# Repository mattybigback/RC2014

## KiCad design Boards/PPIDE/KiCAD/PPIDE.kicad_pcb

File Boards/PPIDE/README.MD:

# PPIDE - 8 bit IDE interface for RC2014

This module is an 8-bit IDE interface based around the 82C55 chip. The design was influenced by the IDE portion of the DiskIO v3 board for the N8VEM/Retrobrew platform. Address decoding is achieved by means of a 74HCT688 comparator.

## Getting up and running

The board will work with [Dr Baker's RomWBW fork](https://github.com/sbelectronics/RomWBW) fork by configuring the PPIDE driver in the platform configuration file. This is achieved by adding the following code to the platform configuration file, located at ```/Source/HBIOS/Config/plt_smb.asm```. If there is already an entry for PPIDE then replace it.

```
PPIDEENABLE     .EQU    FALSE    
PPIDEMODE       .EQU    PPIDEMODE_DIO3  
PPIDETRACE      .EQU    1              
PPIDE8BIT       .EQU    FALSE    
```

You must also add this line to your build config file to enable the PPIDE driver, as it is disabled by default. Build config files are located in the same directory as the platform config files.
```
PPIDEENABLE     .SET    TRUE
```

RomWBW expects the PPIDE hardware to be at haddress 0x20, so by defalt the DIP switches should be set so that A5 is on and the rest are off. You can change the base address in ```/Source/HBIOS/ppide.asm``` by modifying this block of code:

```
#IF (PPIDEMODE == PPIDEMODE_DIO3)
PPIDE_IO_BASE	.EQU	$20
#ENDIF
```

## Board features

* 40 pin IDE for standard desktop IDE drives
* Onboard HDD activity LED
* Header pin for external HDD activity LED
* 5v supply to IDE pin 20 (enabled by bridging JP1)
* Port address selectable by DIP switch

## Bill of materials

| Designator | Component |
|---|---|
| U1 | 74HCT688 |
| U2 | 82C55AZ |
| U3 | 74HCT14 (74HCT04 also suitable) |
| C1 - C3 | 100 nf ceramic capacitor |
| R1 - R2 | 470 Ω |
| R3 - R5 | 10 k |
| RN1 | 10k x 6 resistor network |
| SW1 | 6 way DIP switch |
| P1 | 1 x 39 0.1" right angle pin header |
| P2 | 2 x 20 0.1" right angle pin header |
| P3 | 1 x 2 0.1" straight pin header |
| JP1 | 1 x 2 0.1" straight pin header |
| D1 | 5mm LED |

## Board preview

![alt text][logo]

[logo]: https://github.com/mattybigback/RC2014/blob/master/Boards/PPIDE/PPIDE_small.png "PPIDE Board Render"

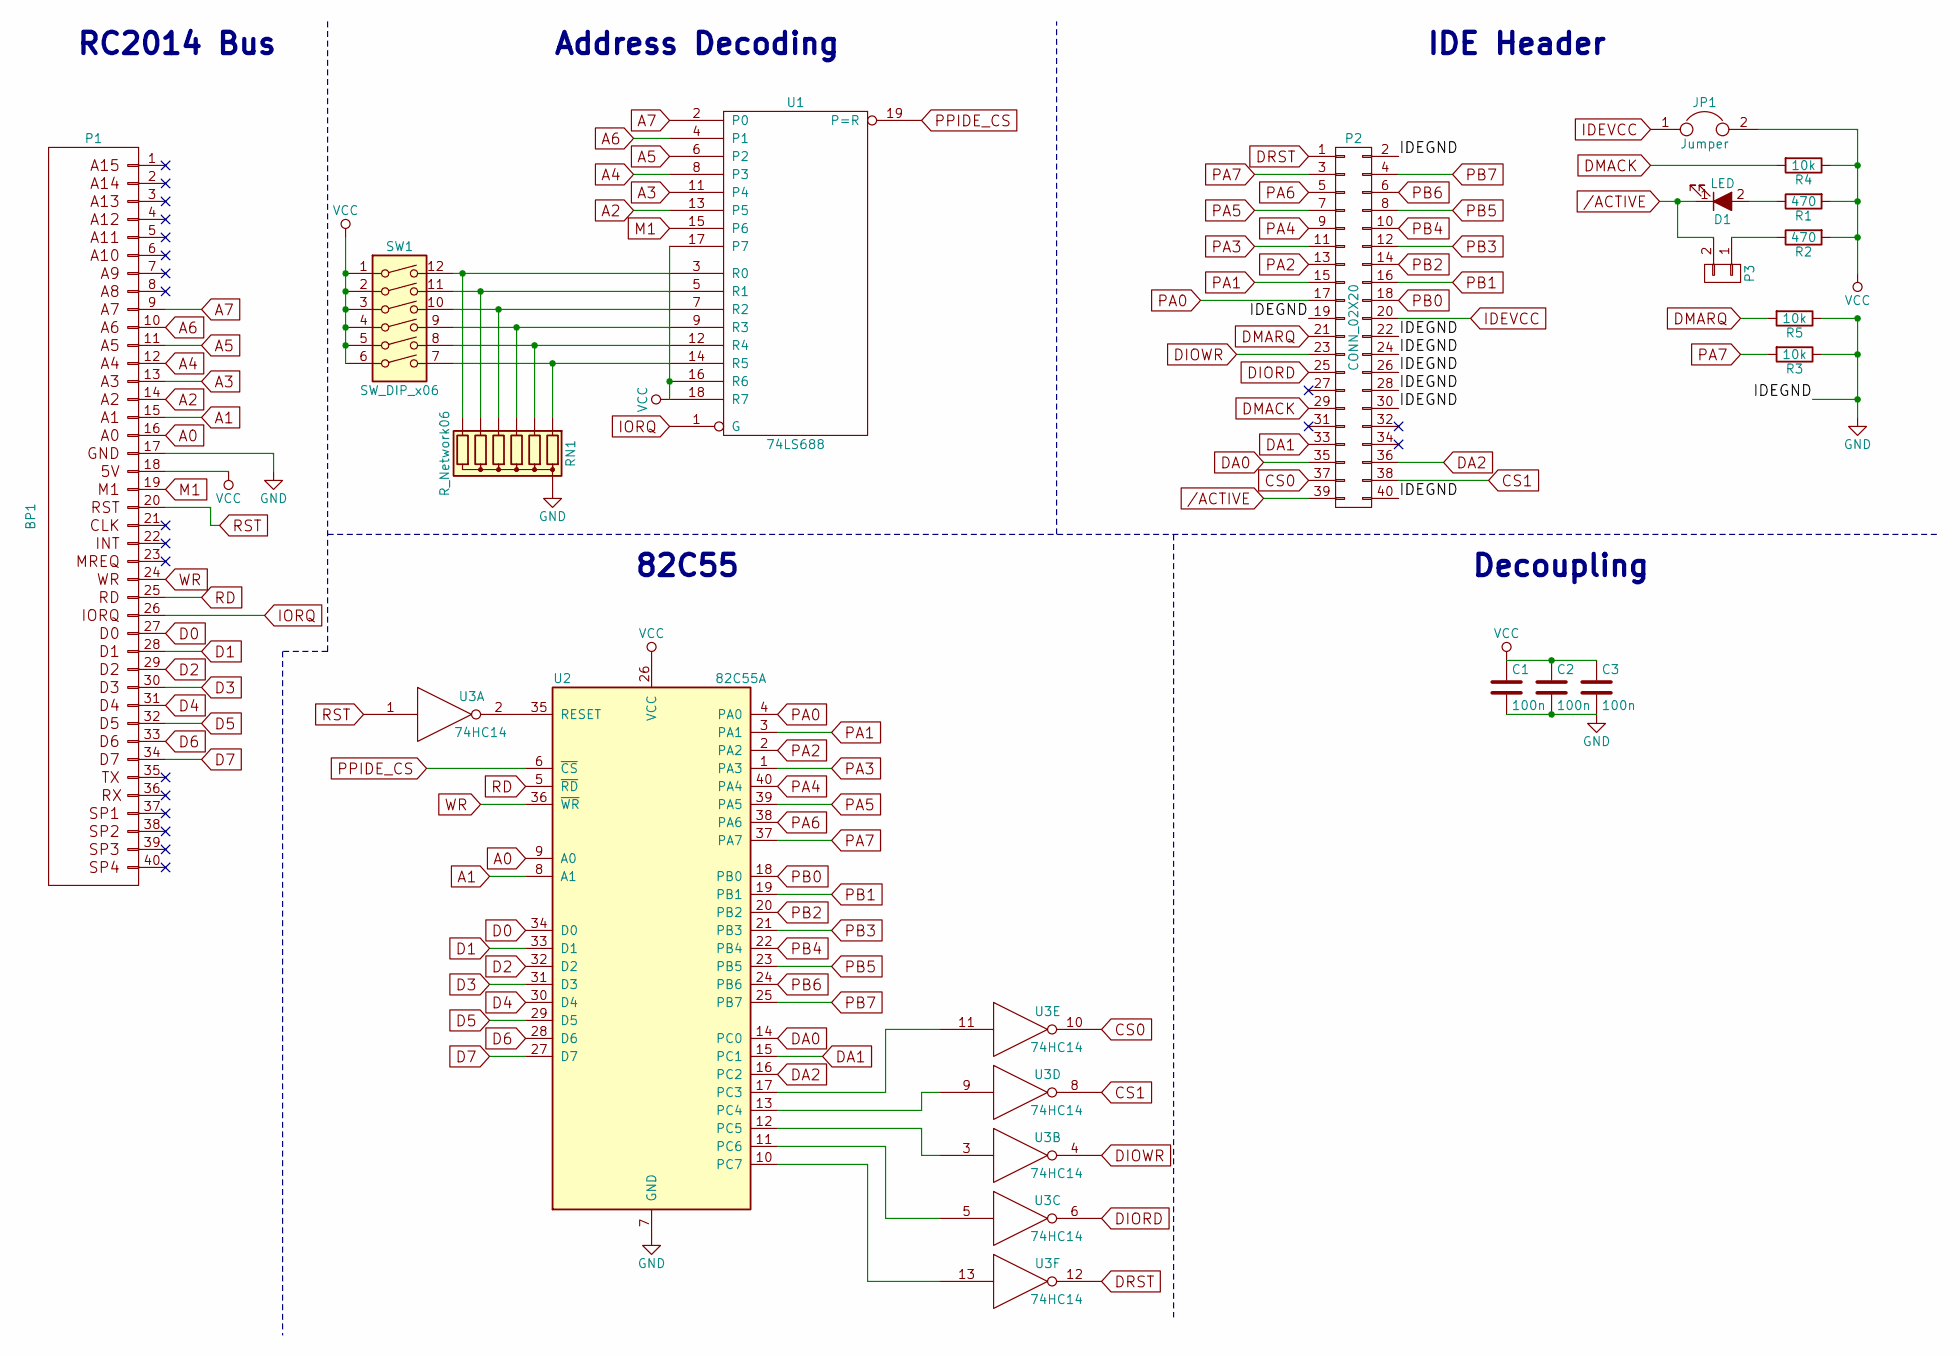
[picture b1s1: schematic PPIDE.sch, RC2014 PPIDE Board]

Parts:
C1, C2, C3: 100n; C_Disc_D10.0mm_W2.5mm_P5.00mm
D1: LED; LED_D5.0mm_FlatTop
JP1: Jumper; Pin_Header_Straight_1x02_Pitch2.54mm
P1: BP1; Pin_Header_Straight_1x39_Pitch2.54mm
P2: CONN_02X20; IDC_Header_Straight_40pins
P3: CONN_01X02; Pin_Header_Straight_1x02_Pitch2.54mm
R1, R2: 470; R_Axial_DIN0207_L6.3mm_D2.5mm_P10.16mm_Horizontal
R3, R4, R5: 10k; R_Axial_DIN0207_L6.3mm_D2.5mm_P10.16mm_Horizontal
RN1: R_Network06; R_Array_SIP7
SW1: SW_DIP_x06; SW_DIP_x6_W7.62mm_Slide
U1: 74LS688; DIP-20_W7.62mm_Socket_LongPads
U2: 82C55A; DIP-40_W15.24mm
U3: 74HC14; DIP-14_W7.62mm_Socket_LongPads

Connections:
/ACTIVE: D1.1 (K), P2.39, P3.2
A0: P1.16, U2.9 (A0)
A1: P1.15, U2.8 (A1)
A2: P1.14, U1.13 (P5)
A3: P1.13, U1.11 (P4)
A4: P1.12, U1.8 (P3)
A5: P1.11, U1.6 (P2)
A6: P1.10, U1.4 (P1)
A7: P1.9, U1.2 (P0)
CS0: P2.37, U3.10
CS1: P2.38, U3.8
D0: P1.27, U2.34 (D0)
D1: P1.28, U2.33 (D1)
D2: P1.29, U2.32 (D2)
D3: P1.30, U2.31 (D3)
D4: P1.31, U2.30 (D4)
D5: P1.32, U2.29 (D5)
D6: P1.33, U2.28 (D6)
D7: P1.34, U2.27 (D7)
DA0: P2.35, U2.14 (PC0)
DA1: P2.33, U2.15 (PC1)
DA2: P2.36, U2.16 (PC2)
DIORD: P2.25, U3.6
DIOWR: P2.23, U3.4
DMACK: P2.29, R4.2
DMARQ: P2.21, R5.2
DRST: P2.1, U3.12
GND: C1.2, C2.2, C3.2, P1.17, P2.2, P2.19, P2.22, P2.24, P2.26, P2.28, P2.30, P2.40, R3.1, R5.1, RN1.1 (common), U1.10 (GND), U2.7 (GND), U3.7 (GND)
IDEVCC: JP1.1, P2.20
IORQ: P1.26, U1.1 (G)
M1: P1.19, U1.15 (P6)
unnamed: D1.2 (A), R1.1
unnamed: P3.1, R2.1
unnamed: RN1.2 (R1), SW1.7, U1.14 (R5)
unnamed: RN1.3 (R2), SW1.8, U1.12 (R4)
unnamed: RN1.4 (R3), SW1.9, U1.9 (R3)
unnamed: RN1.5 (R4), SW1.10, U1.7 (R2)
unnamed: RN1.6 (R5), SW1.11, U1.5 (R1)
unnamed: RN1.7 (R6), SW1.12, U1.3 (R0)
unnamed: U2.10 (PC7), U3.13
unnamed: U2.11 (PC6), U3.5
unnamed: U2.12 (PC5), U3.3
unnamed: U2.13 (PC4), U3.9
unnamed: U2.17 (PC3), U3.11
unnamed: U2.35 (RESET), U3.2
PA0: P2.17, U2.4 (PA0)
PA1: P2.15, U2.3 (PA1)
PA2: P2.13, U2.2 (PA2)
PA3: P2.11, U2.1 (PA3)
PA4: P2.9, U2.40 (PA4)
PA5: P2.7, U2.39 (PA5)
PA6: P2.5, U2.38 (PA6)
PA7: P2.3, R3.2, U2.37 (PA7)
PB0: P2.18, U2.18 (PB0)
PB1: P2.16, U2.19 (PB1)
PB2: P2.14, U2.20 (PB2)
PB3: P2.12, U2.21 (PB3)
PB4: P2.10, U2.22 (PB4)
PB5: P2.8, U2.23 (PB5)
PB6: P2.6, U2.24 (PB6)
PB7: P2.4, U2.25 (PB7)
PPIDE_CS: U1.19 (P=R), U2.6 (~CS~)
RD: P1.25, U2.5 (~RD~)
RST: P1.20, U3.1
VCC: C1.1, C2.1, C3.1, JP1.2, P1.18, R1.2, R2.2, R4.1, SW1.1, SW1.2, SW1.3, SW1.4, SW1.5, SW1.6, U1.16 (R6), U1.17 (P7), U1.18 (R7), U1.20 (VCC), U2.26 (VCC), U3.14 (VCC)
WR: P1.24, U2.36 (~WR~)

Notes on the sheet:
RC2014 Bus
Address Decoding
82C55
IDE Header
Decoupling

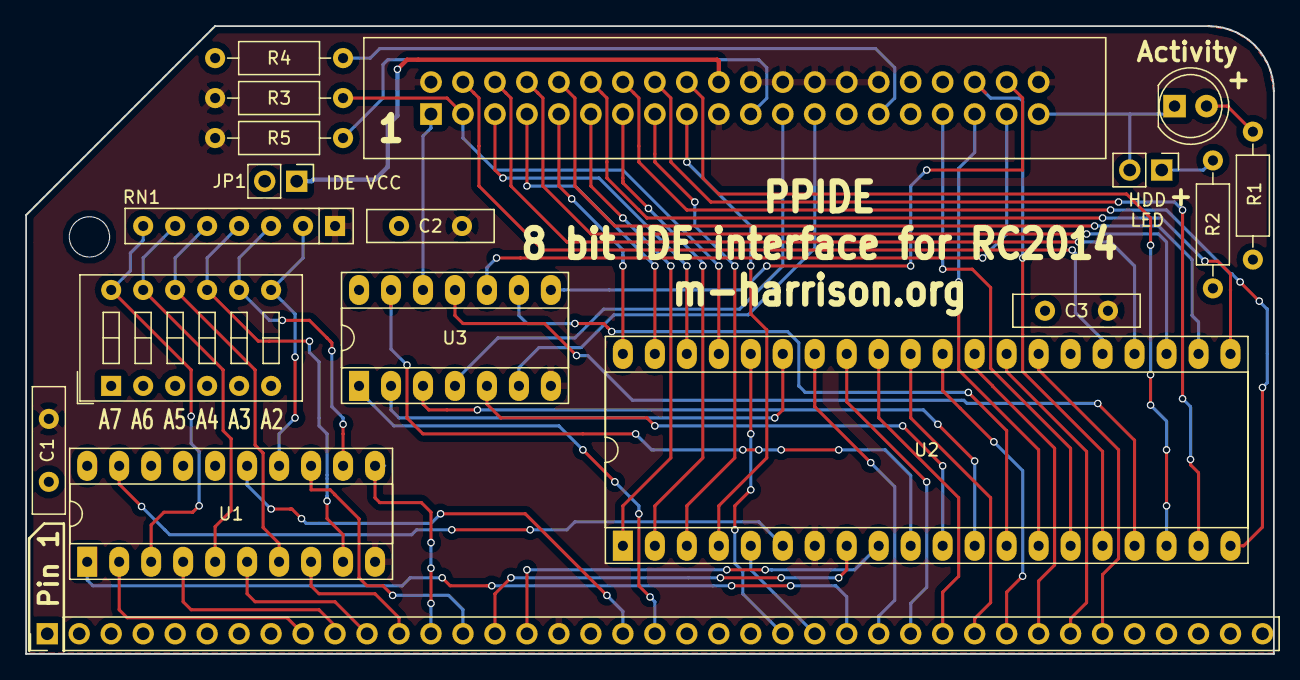
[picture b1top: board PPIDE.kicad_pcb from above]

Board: 2 copper layers, 99.1 x 49.9 mm, 18 parts (0 on the bottom side), 66 nets.

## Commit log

2017-09-14 Create ADCTEST.BAS
    Add ADC test program
2017-09-14 Rename ADCTEST.BAS to BASIC/ADCTEST.BAS
2017-09-15 Update README.MD
    Fixed errors, added information and formatting
2017-09-29 Create README.MD
    Added readme
2017-09-29 Create README.MD
    Added basic readme
